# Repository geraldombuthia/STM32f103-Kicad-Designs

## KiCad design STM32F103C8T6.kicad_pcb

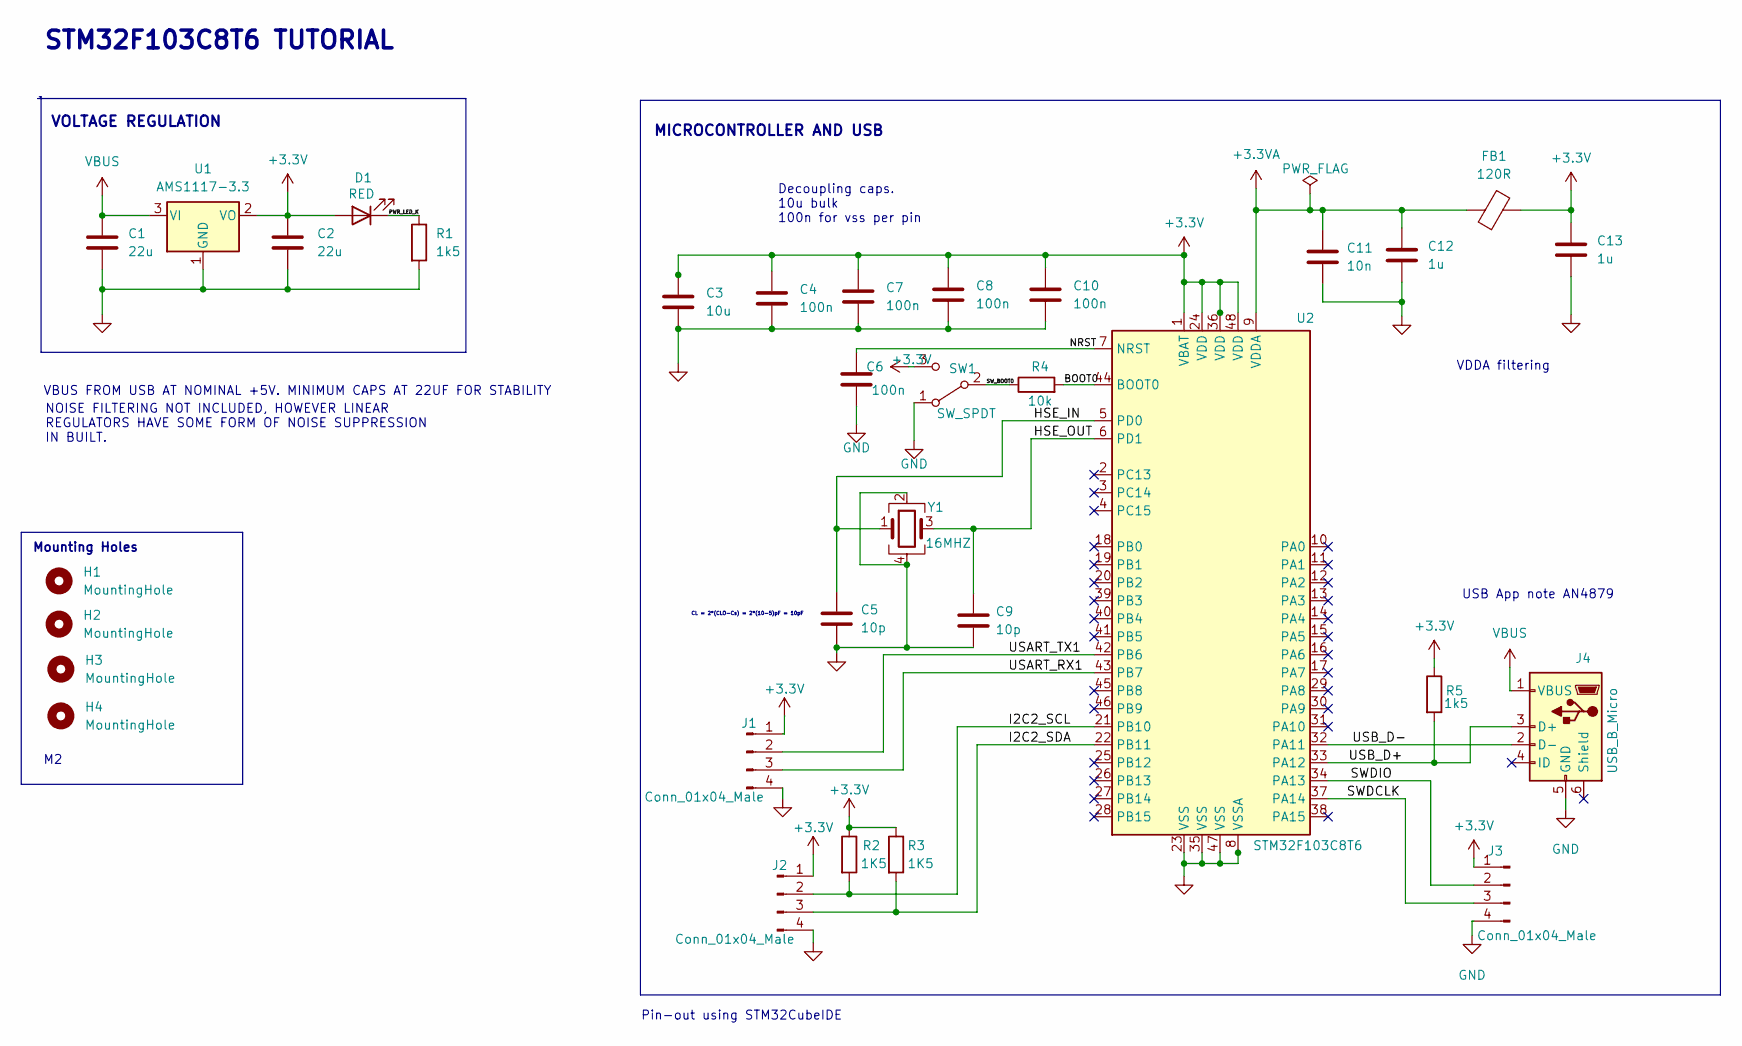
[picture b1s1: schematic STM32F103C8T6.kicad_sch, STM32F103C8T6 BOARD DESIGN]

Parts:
C1, C2: 22u; C_0805_2012Metric
C3: 10u; C_0603_1608Metric
C4, C6, C7, C8, C10: 100n; C_0402_1005Metric
C5, C9: 10p; C_0402_1005Metric
C11: 10n; C_0402_1005Metric
C12, C13: 1u; C_0402_1005Metric
D1: RED; LED_0603_1608Metric
FB1: 120R; L_0603_1608Metric
H1, H2, H3, H4: MountingHole; MountingHole_2.2mm_M2
J1, J2, J3: Conn_01x04_Male; PinHeader_1x04_P2.54mm_Vertical
J4: USB_B_Micro
R1, R5: 1k5; R_0402_1005Metric
R2, R3: 1K5; R_0402_1005Metric
R4: 10k; R_0402_1005Metric
SW1: SW_SPDT; SW_SPDT_PCM12
U1: AMS1117-3.3; SOT-223-3_TabPin2
U2: STM32F103C8T6; LQFP-48_7x7mm_P0.5mm
Y1: 16MHZ; Crystal_SMD_3225-4Pin_3.2x2.5mm

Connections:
+3.3V: C2.1, C3.1, C4.1, C7.1, C8.1, C10.1, C13.1, D1.2 (A), FB1.1, J1.1, J2.1, J3.1, R2.1, R3.1, R5.1, SW1.3 (C), U1.2 (VO), U2.1 (VBAT), U2.24 (VDD), U2.36 (VDD), U2.48 (VDD)
+3.3VA: C11.1, C12.1, FB1.2, U2.9 (VDDA)
/BOOT0: R4.2, U2.44 (BOOT0)
/HSE_IN: C5.1, U2.5 (PD0), Y1.1
/HSE_OUT: C9.1, U2.6 (PD1), Y1.3
/I2C2_SCL: J2.2, R2.2, U2.21 (PB10)
/I2C2_SDA: J2.3, R3.2, U2.22 (PB11)
/NRST: C6.1, U2.7 (NRST)
/PWR_LED_K: D1.1 (K), R1.1
/SWDCLK: J3.3, U2.37 (PA14)
/SWDIO: J3.2, U2.34 (PA13)
/SW_BOOT0: R4.1, SW1.2 (B)
/USART_RX1: J1.3, U2.43 (PB7)
/USART_TX1: J1.2, U2.42 (PB6)
/USB_D+: J4.3 (D+), R5.2, U2.33 (PA12)
/USB_D-: J4.2 (D-), U2.32 (PA11)
GND: C1.2, C2.2, C3.2, C4.2, C5.2, C6.2, C7.2, C8.2, C9.2, C10.2, C11.2, C12.2, C13.2, J1.4, J2.4, J3.4, J4.5 (GND), J4.6 (Shield), R1.2, SW1.1 (A), U1.1 (GND), U2.8 (VSSA), U2.23 (VSS), U2.35 (VSS), U2.47 (VSS), Y1.2, Y1.4
VBUS: C1.1, J4.1 (VBUS), U1.3 (VI)

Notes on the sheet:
VDDA filtering
MICROCONTROLLER AND USB
Pin-out using STM32CubeIDE
Mounting Holes
VOLTAGE REGULATION
NOISE FILTERING NOT INCLUDED, HOWEVER LINEAR REGULATORS HAVE SOME FORM OF NOISE SUPPRESSION IN BUILT.
CL = 2*(CLO-Cs) = 2*(10-5)pF = 10pF
USB App note AN4879
Decoupling caps. 10u bulk 100n for vss per pin
VBUS FROM USB AT NOMINAL +5V. MINIMUM CAPS AT 22UF FOR STABILITY
STM32F103C8T6 TUTORIAL

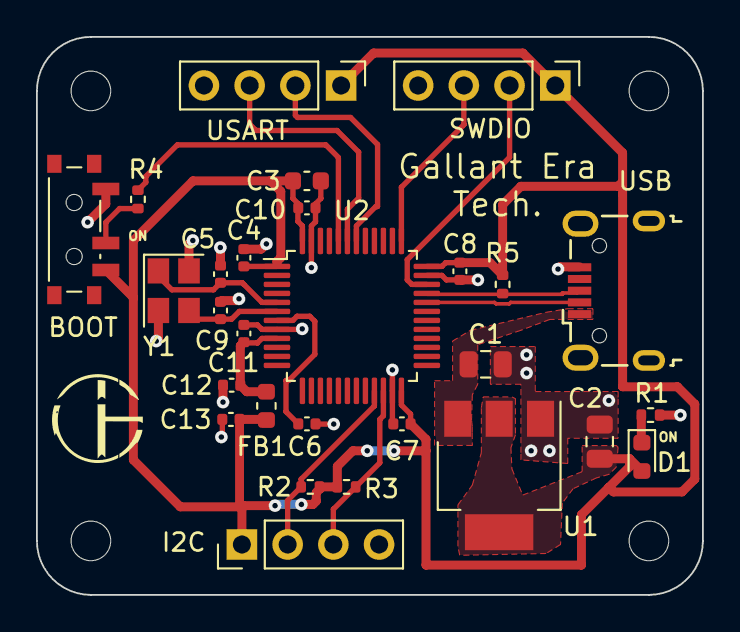
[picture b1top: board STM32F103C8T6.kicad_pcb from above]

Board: 2 copper layers, 37.0 x 31.0 mm, 32 parts (0 on the bottom side), 18 nets.

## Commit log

2023-02-15 Added STM32F103 Design files
